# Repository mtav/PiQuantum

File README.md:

# The epic classical/quantum computer outreach project

The new PiQuantum project is here: https://johnrscott.gitlab.io/PiQuantum/index.html

## `Where quantum information processing meets best coding practice`

Our quantum computer currently has 4 qubits with corresponding Leds used to display
their state and 4 quantum gates (operations) available.

# Operations you can do on the quantum computer

We have separated the list of things you can do on our quantum computer into two
sections. The first are a quantum version of the operations that a regular digital
computer can do,we call these _coherent_. The second set of operations are only available
on a quantum computer.

## Implemented

- 1 & 2 Measure the state
- 1 & 4 Reset to vacuum state
- 3 & 4 Switch to cycling through the state display

- X
- Y
- H
- Control modifier (Hold this and select another gate to do a Controlled version of it)
  e.g Control + X to do CNOT

## Coherent Digital operations

This is a list of the existing operations available:

- **NOT** gate (X) - Changes between red & blue
- **XOR** gate (CNOT) - Changes a 2nd qubit only if the 1st is blue
- **SWAP** gate (SWAP) - Swaps two qubits colours with each other
- **AND** gate (Toff) - A logical AND between two qubits

## Quantum only operations

The operations are:

- **HALF** gate (H) - Mixes the colours of a qubit
- **PHASE** gate (Z) - Changes between the two colour mixes

# Qubit state display (Read out)

We use RGB Leds to display the state of the qubits, there are two display modes
currently. When using our computer, by only using the coherent digital operations there
is no difference between the two display modes. Only when using the _quantum_ only
operations are you able to see a difference.

## Displaying the average state

The default mode is the display averaging state mode. The _coherent_ digital operations
only ever show red or blue. In this display mode we find that doing the **HALF**
operation on a qubit causes the light to change from red -> purple or blue -> white.

## Cycling through the superposition

As mentioned, the display cycling mode does nothing to all combinations of patterns
achieved with only using the _coherent_ digital operations. We find that it does show a
difference between the quantum only operations however. Doing a **HALF** operation to get
a purple qubit shows that when the display mode is changed the qubit will cycle between
being red and blue. This is no accident, the **HALF** operation puts the qubit halfway
between the red and blue state which is why we see purple.

# How it works

# Parts list

- Raspberry Pi
- GPIO Jumper cables
- Breadboard
- RGB LEDs
- Buttons
- Shift registers for serial to parallel

# Software

# Running the code

## Libraries

### WiringPi (for SPI interface)

It might already be installed on the Raspberry Pi. If it's not, it can be install by
cloning git://git.drogon.net/wiringPi and running ./build. The SPI interface also needs
to be enabled in raspi-config.

## Notes on program requirements

- Multiplayer
- Drop in/ drop out number of players
- Multiple game modes
- Should be able to switch between games in the program
- GLOB to exit Program and Pi

# I/O feature (For each player)

- A controller object
- Remapping Leds / Buttons
- Reading push buttons
- Variable Led colours
- Flashing Leds

# State_race game

- Dictionary of patterns
- Read in a list of _cool_ states to show, either randomly pick one or used qubits
  buttons to select the state you want.
- Save button to add a state to the file
- Use controller to build up a state in real time

J Scott, john.scott@bristol.ac.uk
O Thomas, oliver.thomas@bristol.ac.uk

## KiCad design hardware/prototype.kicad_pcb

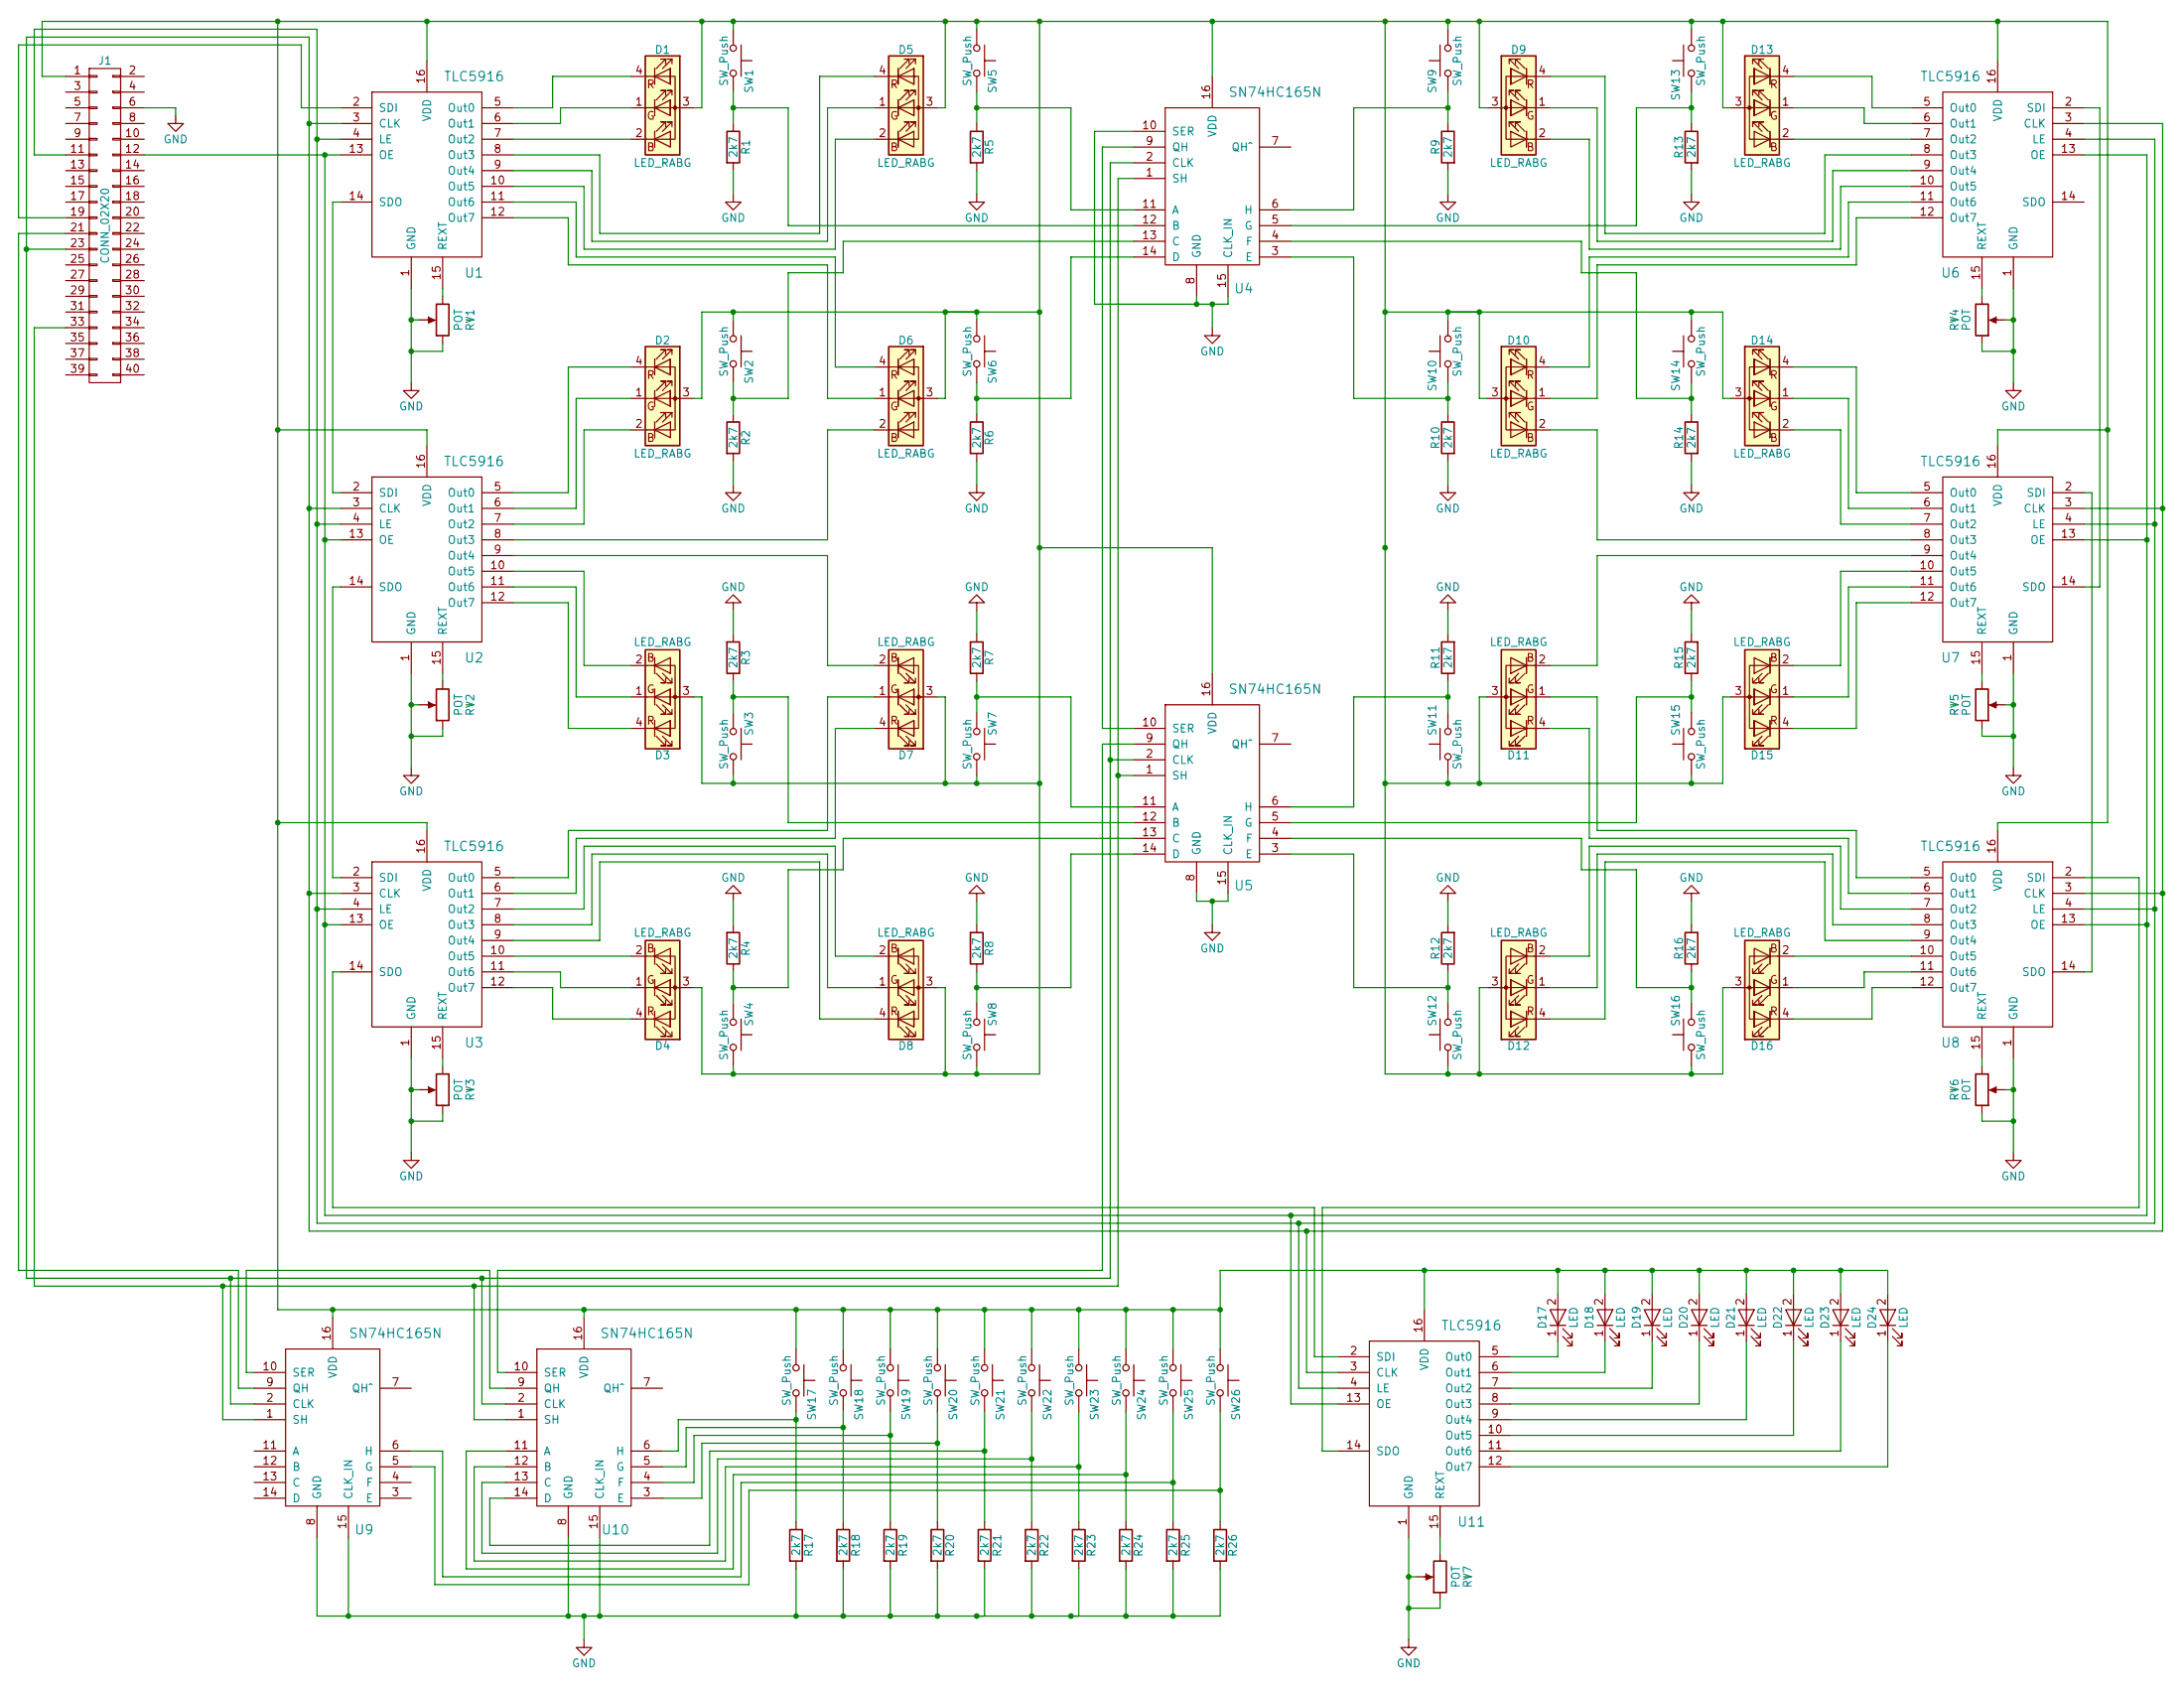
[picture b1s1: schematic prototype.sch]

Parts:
D1, D2, D3, D4, D5, D6, D7, D8, D9, D10, D11, D12, D13, D14, D15, D16: LED_RABG; LED_D5.0mm-4
D17, D18, D19, D20, D21, D22, D23, D24: LED; LED_D5.0mm
J1: CONN_02X20; IDC_Header_Straight_40pins
R1, R2, R3, R4, R5, R6, R7, R8, R9, R10, R11, R12, R13, R14, R15, R16, R17, R18, R19, R20, R21, R22, R23, R24, R25, R26: 2k7; R_Axial_DIN0204_L3.6mm_D1.6mm_P7.62mm_Horizontal
RV1, RV2, RV3, RV4, RV5, RV6, RV7: POT; Vishay_Trimmer_Through_Hole_2.54mm
SW1, SW2, SW3, SW4, SW5, SW6, SW7, SW8, SW9, SW10, SW11, SW12, SW13, SW14, SW15, SW16, SW17, SW18, SW19, SW20, SW21, SW22, SW23, SW24, SW25, SW26: SW_Push; SW_PUSH_5mm_h7.5mm
U1, U2, U3, U6, U7, U8, U11: TLC5916; DIP-16_W7.62mm_LongPads
U4, U5, U9, U10: SN74HC165N; DIP-16_W7.62mm_LongPads

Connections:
GND: J1.6, R1.2, R2.2, R3.2, R4.2, R5.2, R6.2, R7.2, R8.2, R9.2, R10.2, R11.2, R12.2, R13.2, R14.2, R15.2, R16.2, R17.2, R18.2, R19.2, R20.2, R21.2, R22.2, R23.2, R24.2, R25.2, R26.2, RV1.1, RV1.2, RV2.1, RV2.2, RV3.1, RV3.2, RV4.1, RV4.2, RV5.1, RV5.2, RV6.1, RV6.2, RV7.1, RV7.2, U1.1 (GND), U2.1 (GND), U3.1 (GND), U4.8 (GND), U4.10 (SER), U4.15 (CLK_IN), U5.8 (GND), U5.15 (CLK_IN), U6.1 (GND), U7.1 (GND), U8.1 (GND), U9.8 (GND), U9.15 (CLK_IN), U10.8 (GND), U10.15 (CLK_IN), U11.1 (GND)
unnamed: D1.1 (GK), U1.6 (Out1)
unnamed: D1.2 (BK), U1.7 (Out2)
unnamed: D1.3 (A), D2.3 (A), D3.3 (A), D4.3 (A), D5.3 (A), D6.3 (A), D7.3 (A), D8.3 (A), D9.3 (A), D10.3 (A), D11.3 (A), D12.3 (A), D13.3 (A), D14.3 (A), D15.3 (A), D16.3 (A), D17.2 (A), D18.2 (A), D19.2 (A), D20.2 (A), D21.2 (A), D22.2 (A), D23.2 (A), D24.2 (A), J1.1, SW1.1, SW2.1, SW3.1, SW4.1, SW5.1, SW6.1, SW7.1, SW8.1, SW9.1, SW10.1, SW11.1, SW12.1, SW13.1, SW14.1, SW15.1, SW16.1, SW17.1, SW18.1, SW19.1, SW20.1, SW21.1, SW22.1, SW23.1, SW24.1, SW25.1, SW26.1, U1.16 (VDD), U2.16 (VDD), U3.16 (VDD), U4.16 (VDD), U5.16 (VDD), U6.16 (VDD), U7.16 (VDD), U8.16 (VDD), U9.16 (VDD), U10.16 (VDD), U11.16 (VDD)
unnamed: D1.4 (RK), U1.5 (Out0)
unnamed: D2.1 (GK), U2.6 (Out1)
unnamed: D2.2 (BK), U2.7 (Out2)
unnamed: D2.4 (RK), U2.5 (Out0)
unnamed: D3.1 (GK), U2.11 (Out6)
unnamed: D3.2 (BK), U2.10 (Out5)
unnamed: D3.4 (RK), U2.12 (Out7)
unnamed: D4.1 (GK), U3.11 (Out6)
unnamed: D4.2 (BK), U3.10 (Out5)
unnamed: D4.4 (RK), U3.12 (Out7)
unnamed: D5.1 (GK), U1.9 (Out4)
unnamed: D5.2 (BK), U1.10 (Out5)
unnamed: D5.4 (RK), U1.8 (Out3)
unnamed: D6.1 (GK), U1.12 (Out7)
unnamed: D6.2 (BK), U2.8 (Out3)
unnamed: D6.4 (RK), U1.11 (Out6)
unnamed: D7.1 (GK), U3.5 (Out0)
unnamed: D7.2 (BK), U2.9 (Out4)
unnamed: D7.4 (RK), U3.6 (Out1)
unnamed: D8.1 (GK), U3.8 (Out3)
unnamed: D8.2 (BK), U3.7 (Out2)
unnamed: D8.4 (RK), U3.9 (Out4)
unnamed: D9.1 (GK), U6.9 (Out4)
unnamed: D9.2 (BK), U6.10 (Out5)
unnamed: D9.4 (RK), U6.8 (Out3)
unnamed: D10.1 (GK), U6.12 (Out7)
unnamed: D10.2 (BK), U7.8 (Out3)
unnamed: D10.4 (RK), U6.11 (Out6)
unnamed: D11.1 (GK), U8.5 (Out0)
unnamed: D11.2 (BK), U7.9 (Out4)
unnamed: D11.4 (RK), U8.6 (Out1)
unnamed: D12.1 (GK), U8.8 (Out3)
unnamed: D12.2 (BK), U8.7 (Out2)
unnamed: D12.4 (RK), U8.9 (Out4)
unnamed: D13.1 (GK), U6.6 (Out1)
unnamed: D13.2 (BK), U6.7 (Out2)
unnamed: D13.4 (RK), U6.5 (Out0)
unnamed: D14.1 (GK), U7.6 (Out1)
unnamed: D14.2 (BK), U7.7 (Out2)
unnamed: D14.4 (RK), U7.5 (Out0)
unnamed: D15.1 (GK), U7.11 (Out6)
unnamed: D15.2 (BK), U7.10 (Out5)
unnamed: D15.4 (RK), U7.12 (Out7)
unnamed: D16.1 (GK), U8.11 (Out6)
unnamed: D16.2 (BK), U8.10 (Out5)
unnamed: D16.4 (RK), U8.12 (Out7)
unnamed: D17.1 (K), U11.5 (Out0)
unnamed: D18.1 (K), U11.6 (Out1)
unnamed: D19.1 (K), U11.7 (Out2)
unnamed: D20.1 (K), U11.8 (Out3)
unnamed: D21.1 (K), U11.9 (Out4)
unnamed: D22.1 (K), U11.10 (Out5)
unnamed: D23.1 (K), U11.11 (Out6)
unnamed: D24.1 (K), U11.12 (Out7)
unnamed: J1.11, U1.4 (LE), U2.4 (LE), U3.4 (LE), U6.4 (LE), U7.4 (LE), U8.4 (LE), U11.4 (LE)
unnamed: J1.12, U1.13 (OE), U2.13 (OE), U3.13 (OE), U6.13 (OE), U7.13 (OE), U8.13 (OE), U11.13 (OE)
unnamed: J1.19, U1.2 (SDI)
unnamed: J1.21, U9.9 (QH)
unnamed: J1.23, U1.3 (CLK), U2.3 (CLK), U3.3 (CLK), U4.2 (CLK), U5.2 (CLK), U6.3 (CLK), U7.3 (CLK), U8.3 (CLK), U9.2 (CLK), U10.2 (CLK), U11.3 (CLK)
unnamed: J1.33, U4.1 (SH), U5.1 (SH), U9.1 (SH), U10.1 (SH)
unnamed: R1.1, SW1.2, U4.12 (B)
unnamed: R2.1, SW2.2, U4.13 (C)
unnamed: R3.1, SW3.2, U5.12 (B)
unnamed: R4.1, SW4.2, U5.13 (C)
unnamed: R5.1, SW5.2, U4.11 (A)
unnamed: R6.1, SW6.2, U4.14 (D)
unnamed: R7.1, SW7.2, U5.11 (A)
unnamed: R8.1, SW8.2, U5.14 (D)
unnamed: R9.1, SW9.2, U4.6 (H)
unnamed: R10.1, SW10.2, U4.3 (E)
unnamed: R11.1, SW11.2, U5.6 (H)
unnamed: R12.1, SW12.2, U5.3 (E)
unnamed: R13.1, SW13.2, U4.5 (G)
unnamed: R14.1, SW14.2, U4.4 (F)
unnamed: R15.1, SW15.2, U5.5 (G)
unnamed: R16.1, SW16.2, U5.4 (F)
unnamed: R17.1, SW17.2, U10.6 (H)
unnamed: R18.1, SW18.2, U10.5 (G)
unnamed: R19.1, SW19.2, U10.4 (F)
unnamed: R20.1, SW20.2, U10.3 (E)
unnamed: R21.1, SW21.2, U10.14 (D)
unnamed: R22.1, SW22.2, U10.13 (C)
unnamed: R23.1, SW23.2, U10.12 (B)
unnamed: R24.1, SW24.2, U10.11 (A)
unnamed: R25.1, SW25.2, U9.6 (H)
unnamed: R26.1, SW26.2, U9.5 (G)
unnamed: RV1.3, U1.15 (REXT)
unnamed: RV2.3, U2.15 (REXT)
unnamed: RV3.3, U3.15 (REXT)
unnamed: RV4.3, U6.15 (REXT)
unnamed: RV5.3, U7.15 (REXT)
unnamed: RV6.3, U8.15 (REXT)
unnamed: RV7.3, U11.15 (REXT)
unnamed: U1.14 (SDO), U2.2 (SDI)
unnamed: U2.14 (SDO), U3.2 (SDI)
unnamed: U4.9 (QH), U5.10 (SER)
unnamed: U6.2 (SDI), U7.14 (SDO)
unnamed: U7.2 (SDI), U8.14 (SDO)
unnamed: U9.10 (SER), U10.9 (QH)
unnamed: U5.9 (QH), U10.10 (SER)
unnamed: U3.14 (SDO), U11.2 (SDI)
unnamed: U8.2 (SDI), U11.14 (SDO)

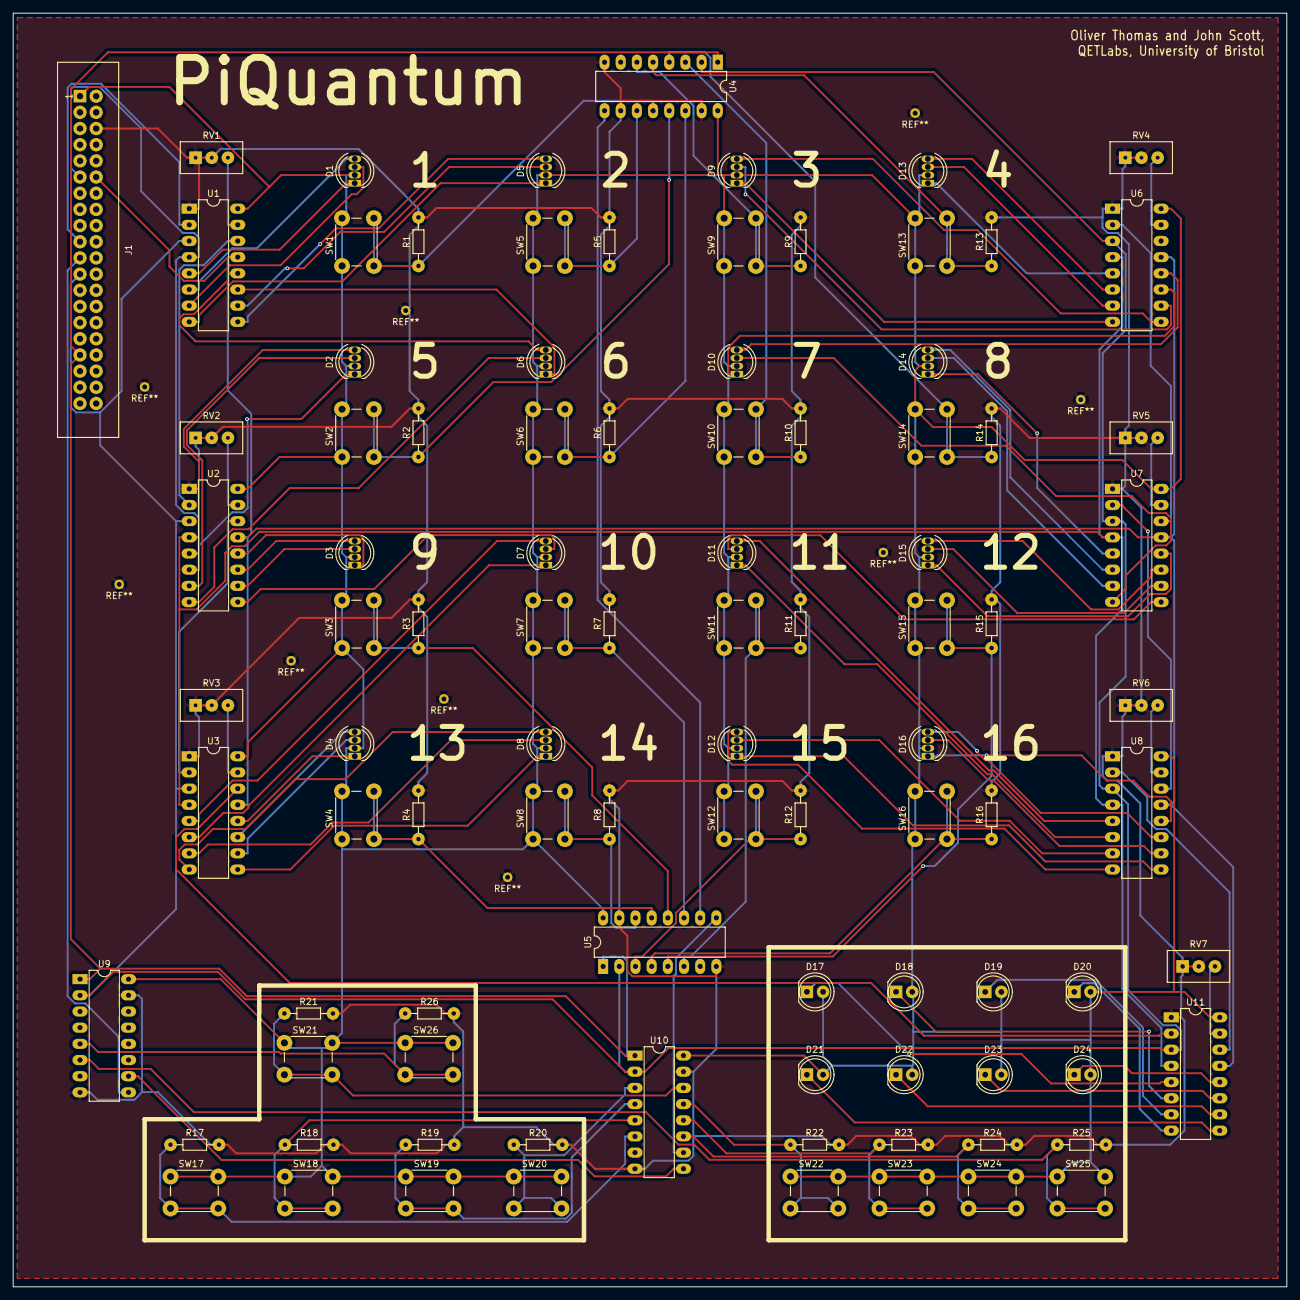
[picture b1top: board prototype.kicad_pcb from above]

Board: 2 copper layers, 200.0 x 200.0 mm, 95 parts (0 on the bottom side), 106 nets.

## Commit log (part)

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2018-12-06 Re-organised folder structure
2018-12-06 Moved docs and notes to folders
2018-12-06 Made a new project for the simulator
2018-12-06 Deleted old html docs
2018-12-06 Added a plan for the new code
2018-12-07 not sure
2018-12-07 tried to revert master/exp merge
2018-12-07 fixed broken reset function
2018-12-07 cant build
2018-12-07 removed trap.c from the make file
2018-12-07 found setup_clock is causing the 2 min crash
2018-12-10 updated outreach plan with suggested jobs
2018-12-10 added figure to plan
2018-12-10 added caption for artist's impression
2018-12-14 added brief descriptions
2019-01-30 working on the main structure
2019-02-05 renamed repo, add src folder for Pi c code
2019-02-05 Added a makefile
2019-02-05 Added an SPI example. Not tested
2019-02-05 Deleted enum, printed return data
2019-02-06 Checked it compiles. Added Makefile clean target
2019-02-06 renamed old dspic code, removed digital folder for now
2019-02-06 Added an SPI class
2019-02-06 Not fixed SPI yet
2019-02-06 Added to readme
2019-02-06 Split SPI stuff over a few files
2019-02-06 Added some more comments
2019-02-06 added ncurses menu example to main.c
2019-02-06 Started working on LED driver
2019-02-07 Tested the spi leds
2019-02-07 Formatted main file
2019-02-07 Changed main to cpp
2019-02-07 Changed comments
2019-02-07 Added a basic menu class
2019-02-07 Added a clear all method
2019-02-07 Not currently working
2019-02-07 Added part of a submenu system
2019-02-07 Minor changes
2019-02-07 slightly less broken than yours :p
2019-02-08 menu now has collumns and qubit control
2019-02-08 ncurses menu stuff
2019-02-08 resized menu so everything fits properly
2019-02-08 added back buttons to all of the options
2019-02-08 Tried to make background static
2019-02-09 cleaned up and madee headers for the menu code
2019-02-09 moved stuff to testing and menu folders
2019-02-11 Added dimming file
2019-02-11 Merge
2019-02-11 Deleted dimming.hpp
2019-02-11 doxygen, renamed the maths dir to mathematics
2019-02-11 installed eigen with sudo apt-get install libeigen3-dev
2019-02-11 created the grand state vector class
2019-02-11 Added a test dimming class
2019-02-11 Menu still not working
2019-02-11 a mess but sorted the passing Eigen matrices to the operator class. time for illegal overloading :p
2019-02-11 Fixed menu sytem
2019-02-12 Made suggestions
2019-02-12 added pauli operators back in
2019-02-12 Added menu stuff
2019-02-12 modified procedural menu system
2019-02-12 Added menus
2019-02-12 moving to new OOP menu system
2019-02-12 Changed add_item to add, fixed back button pos
2019-02-12 added numbers for menu input i.e. 1 selects option 1
2019-02-12 not changing anymore menu stuff
2019-02-12 started on readme, observing best practice by fixing header files with headerguard
2019-02-13 started on buttons.
2019-02-14 added button mapping
2019-02-14 Added object files
2019-02-14 Changed LED driver to use a shared_ptr spi
2019-02-14 added button pin mappings, not reading in any data still.
2019-02-14 Partially finished general LED driver
2019-02-15 added in correct button mappings, still not reading any spi bytes
2019-02-18 Got LEDs 'working'
2019-02-19 Added app
2019-02-19 Changed SpiChannel to singleton
2019-02-19 Added a slightly broken singleton function
2019-02-19 Made LEDs work
2019-02-19 Updated app
2019-02-19 Added minimal bluetooth connection
2019-02-19 Added a sample bluez program
2019-02-19 Added makefile target
2019-02-20 Added some more bluetooth stuff
2019-02-20 added new make file to work on
2019-02-20 SDP record working now, still not connecting
2019-02-20 changed Spi class to have read(int num_bytes) and write(std::vector<unsigned char> bytes)
2019-02-20 Adde singletons, got rid of warnings
2019-02-20 Added wiringPi init class
2019-02-21 Made some changes and now there are segfaults...
2019-02-21 Fixed seg faults
2019-02-21 Tested latest version compiles and runs
2019-02-21 spi.hpp reviewed
2019-02-21 Bluetooth tests
2019-02-22 Added led tests
2019-02-22 Merged and fixed LED problems
2019-02-23 cleaned up master, moved old stuff to old branch and testing to experimental branch
2019-02-24 got two-qubit gates working, using old method as I couldn't workout what the new one did.
2019-02-24 gate benchmarking. Optimisation is needed! -O2
2019-02-24 realised pi is connected so cant time gates.
2019-02-24 qubit index caching.
2019-02-25 benchmarking pi 20 qubits 0.1s/gate, 0.05s/two-qubit gate
2019-02-25 Fixed makefile merge
2019-02-25 nothing
2019-02-25 not sure what I changed. sorry
2019-02-25 Added new makefile
2019-02-25 Updated auto-dependency makefile
2019-02-26 More makefiles
2019-02-26 Deleleted makefile
2019-02-26 Minor changes, tested new makefile
2019-02-26 Cleaned
2019-02-26 benchmarking basic display averaging
2019-02-26 memory speed problems.
2019-02-27 disp averaging
2019-02-27 Tested button reading
2019-02-27 Renamed LED to io
2019-02-27 Added new makefile in
2019-02-27 Seperated LEDs from IO
2019-02-27 Removed all warnings, tested spi-test again
2019-02-27 cleaned up code, changed default display stuff to use the list
2019-02-27 Moved function bodies to .cpp for io
2019-02-27 Started implementing button reading
2019-02-27 cleaned upd the state and display stuff, still taking too long
2019-02-27 Added some matmul benchmarks
2019-02-27 Added display averaging
2019-02-27 use -03
2019-02-27 Tested the display averaging -- 0.3s per 20 qubits
2019-02-27 You can get speed ups with caching tricks
2019-02-27 Made a mistake -- caching is slower
2019-02-28 New caching trick -- down to 0.18s per 20 qubits
2019-02-28 Added some button stuff
2019-02-28 speed
2019-02-28 Updated sim stuff
2019-02-28 Fixing merge
2019-02-28 Added working button class
2019-02-28 Started adding some other math stuff
2019-02-28 Added benchmark to math_test
2019-02-28 Added some benchmarks
2019-02-28 Resolved part of merge
2019-02-28 Added led and button tests
2019-02-28 Added wiring pi setup to io class
2019-02-28 Reduced alarm period to 500
2019-02-28 Added some comment
2019-02-28 Added a byte type
2019-02-28 Modified SPI channel to use only channel zero
2019-02-28 Small improvements to SPI class
2019-02-28 Comments and checked it still compiles
2019-02-28 Made some improvements to io.hpp and io.cpp
2019-02-28 Added comments to io.hpp
2019-02-28 Rearranged io.hpp to make it clearer
2019-02-28 Added deregister to IO class
2019-03-01 Comments
2019-03-01 Rearranged some lines
2019-03-01 Added more maths
2019-03-02 Added single qubit benchmarks
2019-03-02 Added a two qubit operation -- still needs checking
2019-03-02 Added Hadamard class
2019-03-02 Added X, Y and Z ops and also corrected a small bug
2019-03-02 Currently controlled gates not working
2019-03-02 Tested some optimisations
2019-03-02 Added more benchmarking
2019-03-02 Cached atan2 values
2019-03-02 Removed atan2 temporarily
2019-03-02 More benchmarking
2019-03-02 changed disp to only update after gate has acted on qubit, add phase stuff
2019-03-02 Split up into source files -- a bit slower
2019-03-02 Tried to understand the structure of the sgate function
2019-03-03 More tests
2019-03-03 Tried inlining matmul -- no difference
2019-03-03 First attempt really slow -- don't start threads in loops
2019-03-03 Not working yet
2019-03-03 added phase calculation that is working properly now, (normalized and everything!)
2019-03-03 reviewed spi.h&c all good, io is more complex...
2019-03-03 Faster than previous attempt, but still slower than no threads
2019-03-03 Experimenting with optimisations
2019-03-03 Partially manually inlining cmatvec speeds up sgate a bit
2019-03-03 More inlining gives a bigger speed up
2019-03-03 A different variant
2019-03-03 profiling
2019-03-03 without phase caching args of state vect IT IS SLOW
2019-03-03 Benchmarked inlining
2019-03-03 Minor changess
2019-03-04 Copied spi stuff to src
2019-03-04 Added io stuff to final folder
2019-03-04 Need to solve flickering LEDs
2019-04-08 changed makefile in final,
2019-04-08 need to write qubit_state to leds, see final folder
2019-04-08 added qubit led container type
2019-04-10 Progress?????
2019-04-10 QUBIT DISPLAYINGLEDS >?>SD<A:L<>?
2019-04-11 weird led bug?
2019-04-11 smart pointers?
2019-04-11 broken
2019-04-11 unique ptrs?
2019-04-12 hack
2019-04-12 gates BUTTONS AND LEDS WORKING
2019-04-12 fixed merge problem
2019-04-12 display cycling
2019-04-12 remove display options
2019-04-12 Added schematic pdf
2019-04-12 Added zipped
2019-04-12 removed delay
2019-04-12 added newlie to display
2019-04-12 unique ptr testing without LEDS
2019-04-16 changed code to run for 20 qubits. DON'T USE LINKTIME OPT - BREAKS
2019-04-16 added reset button (qubit 1 & 4 together)
2019-04-16 pi display cycling
2019-04-17 memory problem with display cycling after a certain number, depends on which wubit
2019-04-17 adding new qubit class to fix led/button ptr problems
2019-04-17 fixed 1 led problem
2019-04-17 more vectors!
2019-04-18 vector of qubits qith leds & btns finally working. still seg fault at end of prog
2019-04-18 Monumental progress (ish)
2019-04-18 small button bouncing issue
2019-04-25 moved the operator implementation into cpp file
2019-04-25 fixed various mistakes
2019-04-27 warnings but no errors?
2019-04-27 fixed paths for doxygen
2019-04-28 ready to test the display cycling stuff
2019-04-29 removed junk
2019-04-29 Added a timer and an example to main
2019-04-29 fixed bugs f# Please enter the commit message for your changes. Lines starting
2019-04-29 Last commit on experimental, sorry
2019-04-29 Need to fix the horrendous flickering
2019-04-29 Not sure the timing of sigalarm is right
2019-04-29 Checked changing process priority -- not sure it changed anything
2019-04-30 easurement broken
2019-05-02 compiled for demo
2019-05-03 Added more pcb stuff
2019-05-03 More pcb stuff
2019-05-03 Flashing qubits and no crashes?
2019-05-08 NEW and IMPROVED! Implemented arrows keys w/buttons and button trigger on release
2019-05-08 multithreading.
2019-05-09 fixed double flash in cycling mode
2019-05-10 PCB stuff
2019-05-16 starting on dev/input for controller
2019-05-16 Finally got the usb controller input working!
2019-05-16 Controller class working now.
2019-05-16 controller ready to be added to state or main
2019-05-16 started controller branch
2019-05-17 -FLTO causes segfaults... Controller working for direction input
2019-05-17 single qubit gates working with controller
2019-05-17 Hacked two qubit gates CPHASE and CNOT for a demo, need to fix
2019-05-17 buildworks
2019-05-18 adding second state
2019-05-20 Added gerbers
2019-05-20 controller adding player 2
2019-05-20 2 player!
2019-05-20 2 player working ish
2019-05-20 2 controllers
2019-05-20 sometimes there are memory bad-allocs. Not great
2019-05-20 Fixed ALL compiler warnings??
2019-05-21 separate thread timers, working with 2 players
2019-05-21 Added png
2019-05-21 Added front on picture
2019-05-23 added exec sudo ./main
2019-05-23 working on function passing
2019-05-23 templates?
2019-05-23 before I forget
2019-05-23 Added a test file
2019-05-23 button mapping is working now, usr std::bind to pass with no args
2019-05-23 Fixed alarm
2019-05-23 Merged
2019-05-23 need to add the Game class now and sort out threading for each controller
2019-05-24 SEGFAULT IS NO MORE
2019-05-24 changing button mapping functions works in real time
2019-05-24 added controllers reading from member variables, needed for applying gates on the "cursor" qubit without waiting/blocking
2019-05-24 imaking games classes
2019-05-24 what am I doing
2019-05-24 flashing working but not very elegant
2019-05-24 two qubit gates not working, need to do some threading i think
2019-05-25 removed redundant controller manager and put that in the player class
2019-05-25 comments REMOVED
2019-05-25 The Game class is getting rather large...
2019-05-31 work to do...
2019-06-03 Added mapping
2019-06-03 added in support for 16 leds
2019-06-03 syntax error
2019-06-03 working Piquantum v1
2019-06-03 Changed SoftPWM_TM rate
2019-06-03 fixed direction cycling
2019-06-03 fixed bugs
2019-06-05 broken sorry
2019-06-13 adding controls documentation
2019-06-13 ignoring files generated by dolphin and make
